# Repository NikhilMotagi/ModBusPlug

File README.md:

# ModbusPlug

USB Type-C to RS-485 Modbus RTU dongle for phones, rugged tablets, and laptops.

ModbusPlug is an open-source USB-C to RS-485 adapter designed for field engineers who work from rugged phones and tablets instead of laptops. The project was created to showcase PCB design skills while providing a compact, Type-C-native alternative to the usual USB-A Modbus dongles.

<p align="center"><em>AI-generated concept render of a possible enclosure. The real shell is not designed yet (see Help Wanted).</em></p>

---

## Features

- USB Type-C receptacle (USB 2.0 full-speed)
- USB-to-UART bridge using CP2102N
- RS-485 interface using SN65HVD75
- IEC 61000-4-2 ±12 kV contact ESD protection on bus pins
- Power status LED and UART TX/RX activity LEDs
- Fixed 120 Ω termination
- Compact PCB layout

---

## Design Goals

The objective of this project was to:

- Create a Type-C-native Modbus RTU adapter
- Remove the need for USB-A adapters and laptops in field work
- Demonstrate PCB design and hardware integration skills
- Provide an open-source reference design for engineers and hobbyists

---

## Block Diagram

---

## Images

### PCB

|||
|--|--|
|||

### Layout

|||
|--|--|
|||

---

## Manufacturing Status

> ⚠️ Design Complete — Not Yet Manufactured

This repository currently contains the completed design files and manufacturing outputs. Physical prototypes have not yet been fabricated or tested.

---

## Help Wanted: The Enclosure

The PCB is done, but the shell is not. I'm an electronics engineer, and enclosure CAD is not where I want to spend my weekends.

If you'd like to design a case for this board:

- Rugged and 3D-printable (FDM or resin)
- Openings for the USB-C port, RS-485 terminals, and LEDs
- Open a pull request with STEP/STL files in an `Illustration/` folder and you'll be credited here

---

## License

This project is released under the MIT License.

See the `LICENSE` file for details.

---

## Author

Designed by **Nikhil Motagi**.

If you find this project useful, feel free to star the repository and share your feedback.

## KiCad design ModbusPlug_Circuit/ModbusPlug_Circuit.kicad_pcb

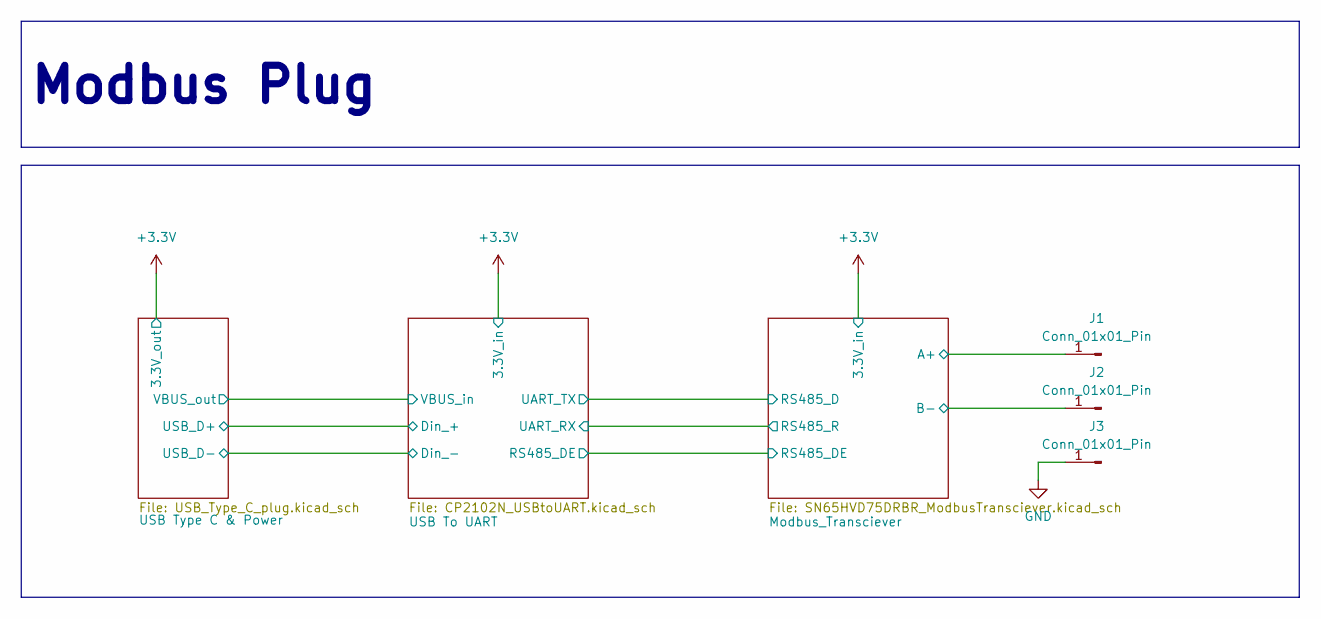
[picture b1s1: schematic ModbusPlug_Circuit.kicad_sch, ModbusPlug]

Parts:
J1, J2, J3: Conn_01x01_Pin; SolderWirePad_1x01_SMD_1x2mm

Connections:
/Modbus_Transciever/A+: J1.1; also elsewhere on the board
/Modbus_Transciever/B-: J2.1; also elsewhere on the board
GND: J3.1; also elsewhere on the board

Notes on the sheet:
Modbus Plug

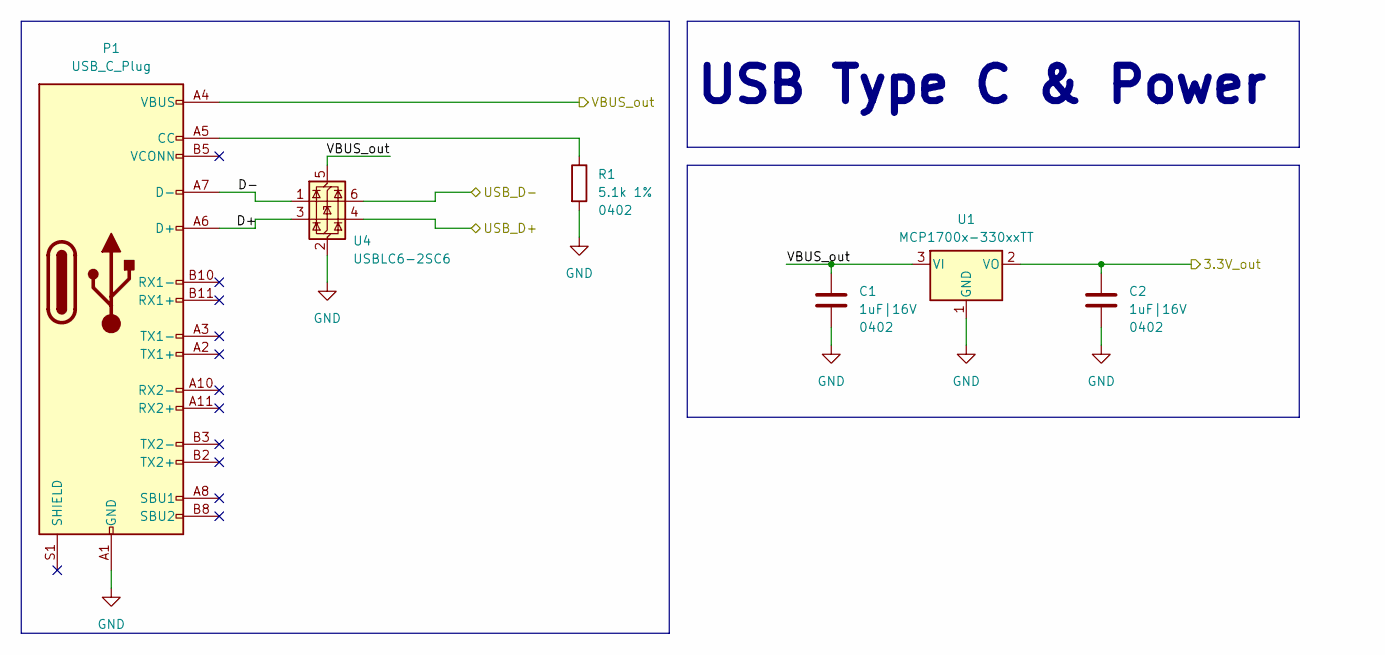
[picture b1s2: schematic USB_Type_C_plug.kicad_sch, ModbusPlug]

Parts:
C1, C2: 1uF|16V; C_0402_1005Metric
P1: USB_C_Plug; GCT_USB4155-03-C_REVA; PARTREV A
R1: 5.1k 1%; R_0402_1005Metric
U1: MCP1700x-330xxTT; SOT-23
U4: USBLC6-2SC6; SOT-23-6

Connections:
+3.3V: C2.1, U1.2 (VO); also elsewhere on the board
/USB To UART/Din_+: U4.4 (I/O2); also elsewhere on the board
/USB To UART/Din_-: U4.6 (I/O1); also elsewhere on the board
/USB Type C & Power/D+: P1.A6 (D+), P1.B6 (D+), U4.3 (I/O2)
/USB Type C & Power/D-: P1.A7 (D-), P1.B7 (D-), U4.1 (I/O1)
/USB Type C & Power/VBUS_out: C1.1, P1.A4 (VBUS), P1.A9 (VBUS), P1.B4 (VBUS), P1.B9 (VBUS), U1.3 (VI), U4.5 (VBUS); also elsewhere on the board
GND: C1.2, C2.2, P1.A1 (GND), P1.A12 (GND), P1.B1 (GND), P1.B12 (GND), R1.2, U1.1 (GND), U4.2 (GND); also elsewhere on the board
unnamed: P1.A5 (CC), R1.1

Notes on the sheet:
USB Type C & Power

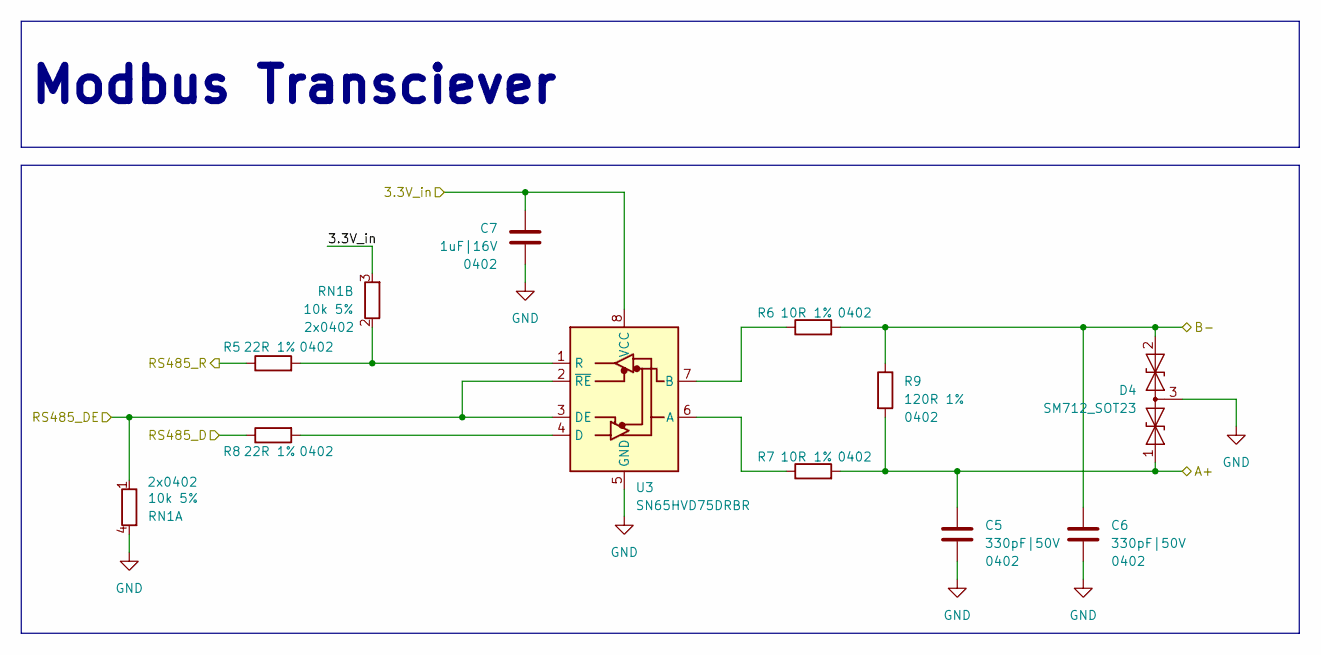
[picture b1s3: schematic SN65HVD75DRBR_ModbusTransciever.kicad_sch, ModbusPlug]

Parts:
C5, C6: 330pF|50V; C_0402_1005Metric
C7: 1uF|16V; C_0402_1005Metric
D4: SM712_SOT23; SOT-23
R5, R8: 22R 1%; R_0402_1005Metric
R6, R7: 10R 1%; R_0402_1005Metric
R9: 120R 1%; R_0402_1005Metric
RN1: 10k 5%; R_Array_Convex_2x0402
U3: SN65HVD75DRBR; VSON-8-1EP_3x3mm_P0.65mm_EP1.65x2.4mm

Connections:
+3.3V: C7.1, RN1.3 (R2.2), U3.8 (VCC); also elsewhere on the board
/Modbus_Transciever/A+: C5.1, D4.1 (A1), R7.2, R9.2; also elsewhere on the board
/Modbus_Transciever/B-: C6.1, D4.2 (A2), R6.2, R9.1; also elsewhere on the board
/Modbus_Transciever/RS485_D: R8.1; also elsewhere on the board
/Modbus_Transciever/RS485_DE: RN1.1 (R1.1), U3.2 (~RE), U3.3 (DE); also elsewhere on the board
/Modbus_Transciever/RS485_R: R5.1; also elsewhere on the board
GND: C5.2, C6.2, C7.2, D4.3 (common), RN1.4 (R1.2), U3.5 (GND), U3.9 (EPad); also elsewhere on the board
unnamed: R5.2, RN1.2 (R2.1), U3.1 (R)
unnamed: R7.1, U3.6 (A)
unnamed: R6.1, U3.7 (B)
unnamed: R8.2, U3.4 (D)

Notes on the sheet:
Modbus Transciever

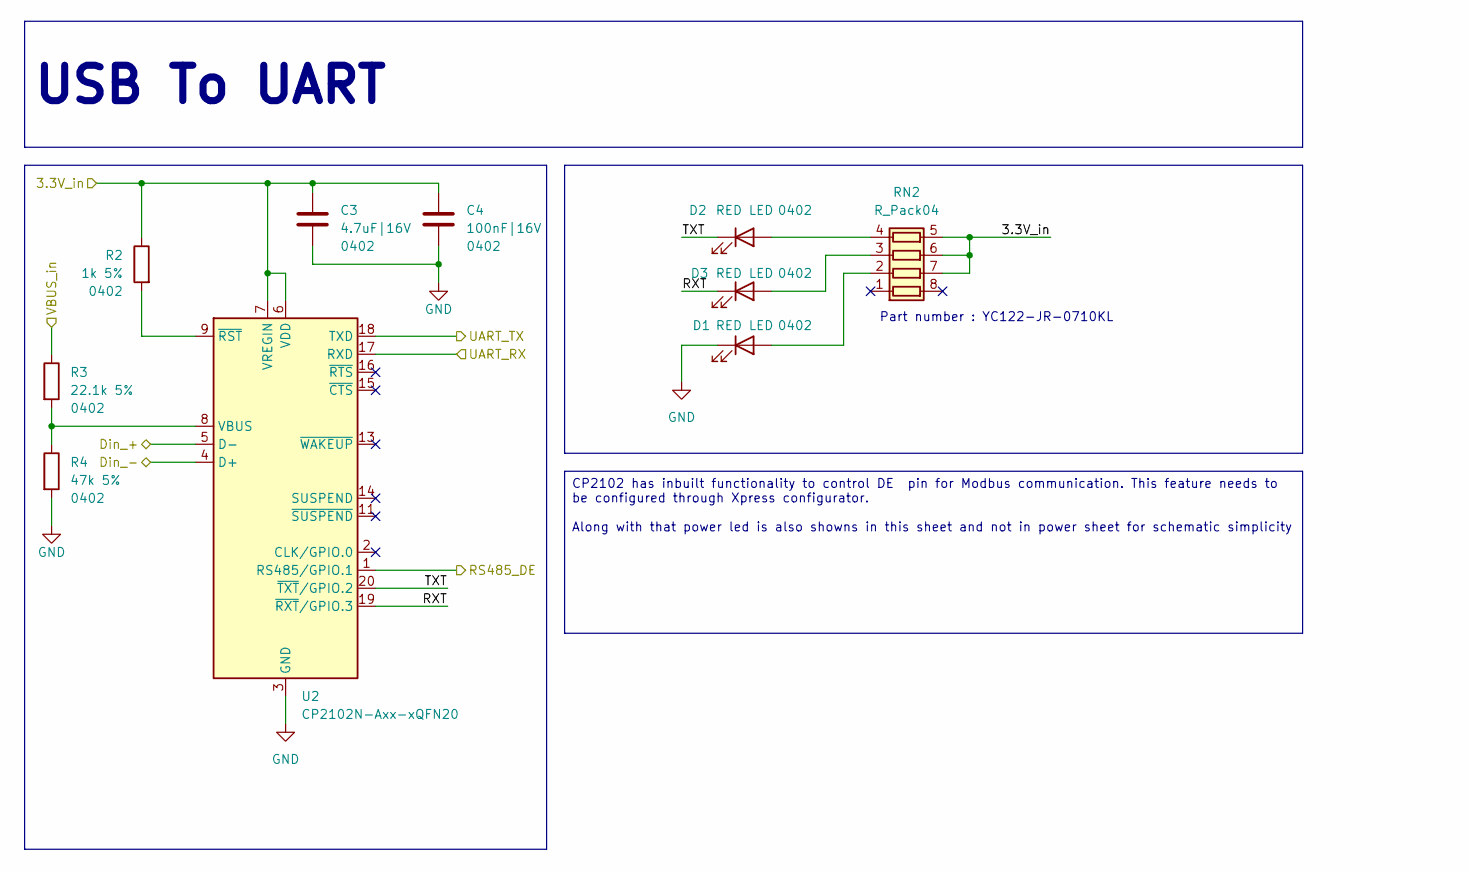
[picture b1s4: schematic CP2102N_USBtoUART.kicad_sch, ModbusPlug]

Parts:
C3: 4.7uF|16V; C_0402_1005Metric
C4: 100nF|16V; C_0402_1005Metric
D1, D2, D3: RED LED; LED_0402_1005Metric
R2: 1k 5%; R_0402_1005Metric
R3: 22.1k 5%; R_0402_1005Metric
R4: 47k 5%; R_0402_1005Metric
RN2: R_Pack04; R_Array_Convex_4x0402
U2: CP2102N-Axx-xQFN20; SiliconLabs_QFN-20-1EP_3x3mm_P0.5mm_EP1.8x1.8mm

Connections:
+3.3V: C3.1, C4.1, R2.1, RN2.5 (R4.2), RN2.6 (R3.2), RN2.7 (R2.2), U2.6 (VDD), U2.7 (VREGIN); also elsewhere on the board
/Modbus_Transciever/RS485_D: U2.18 (TXD); also elsewhere on the board
/Modbus_Transciever/RS485_DE: U2.1 (RS485/GPIO.1); also elsewhere on the board
/Modbus_Transciever/RS485_R: U2.17 (RXD); also elsewhere on the board
/USB To UART/Din_+: U2.5 (D-); also elsewhere on the board
/USB To UART/Din_-: U2.4 (D+); also elsewhere on the board
/USB To UART/RXT: D3.1 (K), U2.19 (~RXT/GPIO.3)
/USB To UART/TXT: D2.1 (K), U2.20 (~TXT/GPIO.2)
/USB Type C & Power/VBUS_out: R3.1; also elsewhere on the board
GND: C3.2, C4.2, D1.1 (K), R4.2, U2.3 (GND), U2.12 (GND), U2.21 (GND); also elsewhere on the board
unnamed: D1.2 (A), RN2.2 (R2.1)
unnamed: D2.2 (A), RN2.4 (R4.1)
unnamed: D3.2 (A), RN2.3 (R3.1)
unnamed: R3.2, R4.1, U2.8 (VBUS)
unnamed: R2.2, U2.9 (~RST)

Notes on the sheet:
Part number : YC122-JR-0710KL
CP2102 has inbuilt functionality to control DE pin for Modbus communication. This feature needs to be configured through Xpress configurator. Along with that power led is also showns in this sheet and not in power sheet for schematic simplicity
USB To UART

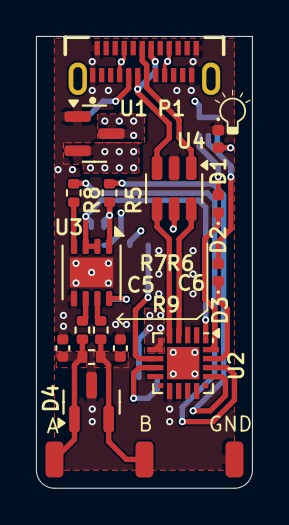
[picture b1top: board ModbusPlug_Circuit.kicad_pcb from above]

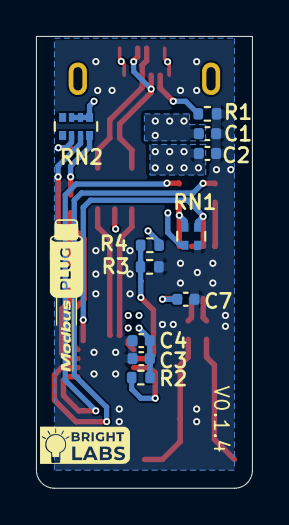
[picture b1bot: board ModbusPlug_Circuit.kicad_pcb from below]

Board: 4 copper layers, 12.0 x 25.1 mm, 30 parts (11 on the bottom side), 24 nets.

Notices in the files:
README.md:
License: MIT
